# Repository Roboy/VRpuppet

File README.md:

# VRpuppet
An actor struggles to die onstage, but a puppet has to struggle to live

## Installation
Clone the repo into your catkin workspace and build it   

    $ cd path_to_catkin_ws/src
    $ git clone --recurse-submodules https://github.com/Roboy/VRpuppet 
    $ cd ..
    $ catkin_make  
    
Source your workspace  

    $ . devel/setup.bash

## Before you start
Make sure the Host IP as well as the Wifi network and password in VRPuppet/hardware/m3/esp/m3_conrol/src/main.c are set to the correct network (e.g. roboy).   

Then flash VRPuppet/hardware/m3/esp/m3_conrol/src/main.c on to all M3 boards. See M3 Readme.md for how to flash.

## Running the VRCage GUI
In a terminal window start a ROScore  

    $ roscore

In a second terminal window navigate to your catkin workspace, source it as seen above and then start up the VRPuppet Gui by runnung
    
    $ rosrun rqt_gui rqt_gui

and then from the dropdown menu *Plugins->Roboy* choose *vr puppets demo*.  

When operating together with OUI team you might also need to set up a **rosbridge server**, if OUI doesn't have a Linux partition on hand.  

To send commands to the linear actuators  press the GUI's serial node button.  

(**Attention**: the Arduino Mega as well as the motorcontrol shield suffered greatly during the hackathon and should be replaced before resuming operation!)

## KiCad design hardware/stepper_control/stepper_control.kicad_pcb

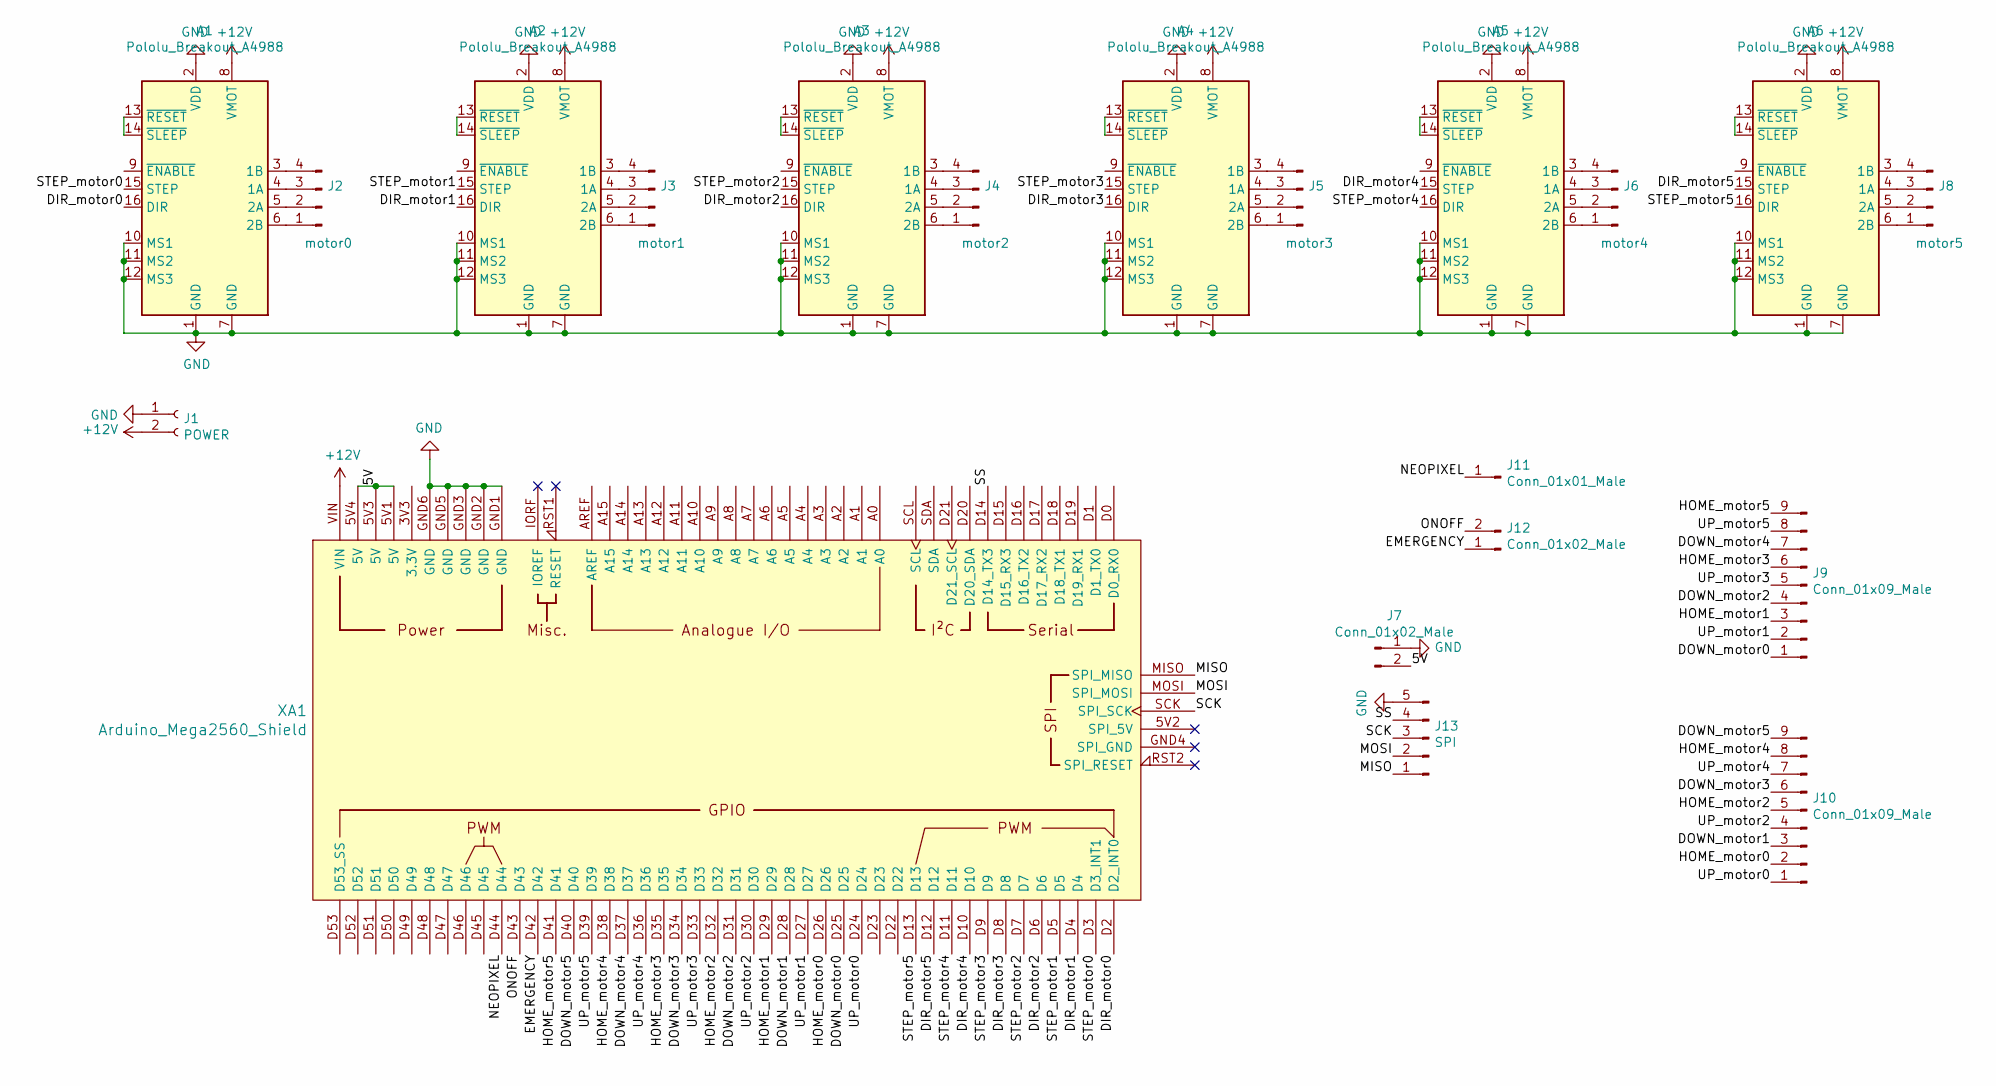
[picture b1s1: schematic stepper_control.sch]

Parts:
A1, A2, A3, A4, A5, A6: Pololu_Breakout_A4988; Pololu_Breakout-16_15.2x20.3mm
J1: POWER; Wago_2060_2_SMD
J2: motor0; PinHeader_1x04_P2.54mm_Vertical
J3: motor1; PinHeader_1x04_P2.54mm_Vertical
J4: motor2; PinHeader_1x04_P2.54mm_Vertical
J5: motor3; PinHeader_1x04_P2.54mm_Vertical
J6: motor4; PinHeader_1x04_P2.54mm_Vertical
J7, J12: Conn_01x02_Male; PinHeader_1x02_P2.54mm_Vertical
J8: motor5; PinHeader_1x04_P2.54mm_Vertical
J9, J10: Conn_01x09_Male; PinHeader_1x09_P2.54mm_Vertical
J11: Conn_01x01_Male; PinHeader_1x01_P2.54mm_Vertical
J13: SPI; PinHeader_1x05_P2.54mm_Vertical
XA1: Arduino_Mega2560_Shield

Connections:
+12V: A1.8 (VMOT), A2.8 (VMOT), A3.8 (VMOT), A4.8 (VMOT), A5.8 (VMOT), A6.8 (VMOT), J1.2, XA1.VIN
/5V: J7.2, XA1.5V1 (5V), XA1.5V3 (5V), XA1.5V4 (5V)
/DIR_motor0: A1.16 (DIR), XA1.D2 (D2_INT0)
/DIR_motor1: A2.16 (DIR), XA1.D4
/DIR_motor2: A3.16 (DIR), XA1.D6
/DIR_motor3: A4.16 (DIR), XA1.D8
/DIR_motor4: A5.15 (STEP), XA1.D10
/DIR_motor5: A6.15 (STEP), XA1.D12
/DOWN_motor0: J9.1, XA1.D25
/DOWN_motor1: J10.3, XA1.D28
/DOWN_motor2: J9.4, XA1.D31
/DOWN_motor3: J10.6, XA1.D34
/DOWN_motor4: J9.7, XA1.D37
/DOWN_motor5: J10.9, XA1.D40
/EMERGENCY: J12.1, XA1.D42
/HOME_motor0: J10.2, XA1.D26
/HOME_motor1: J9.3, XA1.D29
/HOME_motor2: J10.5, XA1.D32
/HOME_motor3: J9.6, XA1.D35
/HOME_motor4: J10.8, XA1.D38
/HOME_motor5: J9.9, XA1.D41
/MISO: J13.1, XA1.MISO (SPI_MISO)
/MOSI: J13.2, XA1.MOSI (SPI_MOSI)
/NEOPIXEL: J11.1, XA1.D44
/ONOFF: J12.2, XA1.D43
/SCK: J13.3, XA1.SCK (SPI_SCK)
/SS: J13.4, XA1.D14 (D14_TX3)
/STEP_motor0: A1.15 (STEP), XA1.D3 (D3_INT1)
/STEP_motor1: A2.15 (STEP), XA1.D5
/STEP_motor2: A3.15 (STEP), XA1.D7
/STEP_motor3: A4.15 (STEP), XA1.D9
/STEP_motor4: A5.16 (DIR), XA1.D11
/STEP_motor5: A6.16 (DIR), XA1.D13
/UP_motor0: J10.1, XA1.D24
/UP_motor1: J9.2, XA1.D27
/UP_motor2: J10.4, XA1.D30
/UP_motor3: J9.5, XA1.D33
/UP_motor4: J10.7, XA1.D36
/UP_motor5: J9.8, XA1.D39
GND: A1.1 (GND), A1.2 (VDD), A1.7 (GND), A1.10 (MS1), A1.11 (MS2), A1.12 (MS3), A2.1 (GND), A2.2 (VDD), A2.7 (GND), A2.10 (MS1), A2.11 (MS2), A2.12 (MS3), A3.1 (GND), A3.2 (VDD), A3.7 (GND), A3.10 (MS1), A3.11 (MS2), A3.12 (MS3), A4.1 (GND), A4.2 (VDD), A4.7 (GND), A4.10 (MS1), A4.11 (MS2), A4.12 (MS3), A5.1 (GND), A5.2 (VDD), A5.7 (GND), A5.10 (MS1), A5.11 (MS2), A5.12 (MS3), A6.1 (GND), A6.2 (VDD), A6.7 (GND), A6.10 (MS1), A6.11 (MS2), A6.12 (MS3), J1.1, J7.1, J13.5, XA1.GND1 (GND), XA1.GND2 (GND), XA1.GND3 (GND), XA1.GND5 (GND), XA1.GND6 (GND)
unnamed: A1.3 (1B), J2.4
unnamed: A1.4 (1A), J2.3
unnamed: A1.5 (2A), J2.2
unnamed: A1.6 (2B), J2.1
unnamed: A1.13 (~RESET), A1.14 (~SLEEP)
unnamed: A2.3 (1B), J3.4
unnamed: A2.4 (1A), J3.3
unnamed: A2.5 (2A), J3.2
unnamed: A2.6 (2B), J3.1
unnamed: A2.13 (~RESET), A2.14 (~SLEEP)
unnamed: A3.3 (1B), J4.4
unnamed: A3.4 (1A), J4.3
unnamed: A3.5 (2A), J4.2
unnamed: A3.6 (2B), J4.1
unnamed: A3.13 (~RESET), A3.14 (~SLEEP)
unnamed: A4.3 (1B), J5.4
unnamed: A4.4 (1A), J5.3
unnamed: A4.5 (2A), J5.2
unnamed: A4.6 (2B), J5.1
unnamed: A4.13 (~RESET), A4.14 (~SLEEP)
unnamed: A5.3 (1B), J6.4
unnamed: A5.4 (1A), J6.3
unnamed: A5.5 (2A), J6.2
unnamed: A5.6 (2B), J6.1
unnamed: A5.13 (~RESET), A5.14 (~SLEEP)
unnamed: A6.3 (1B), J8.4
unnamed: A6.4 (1A), J8.3
unnamed: A6.5 (2A), J8.2
unnamed: A6.6 (2B), J8.1
unnamed: A6.13 (~RESET), A6.14 (~SLEEP)

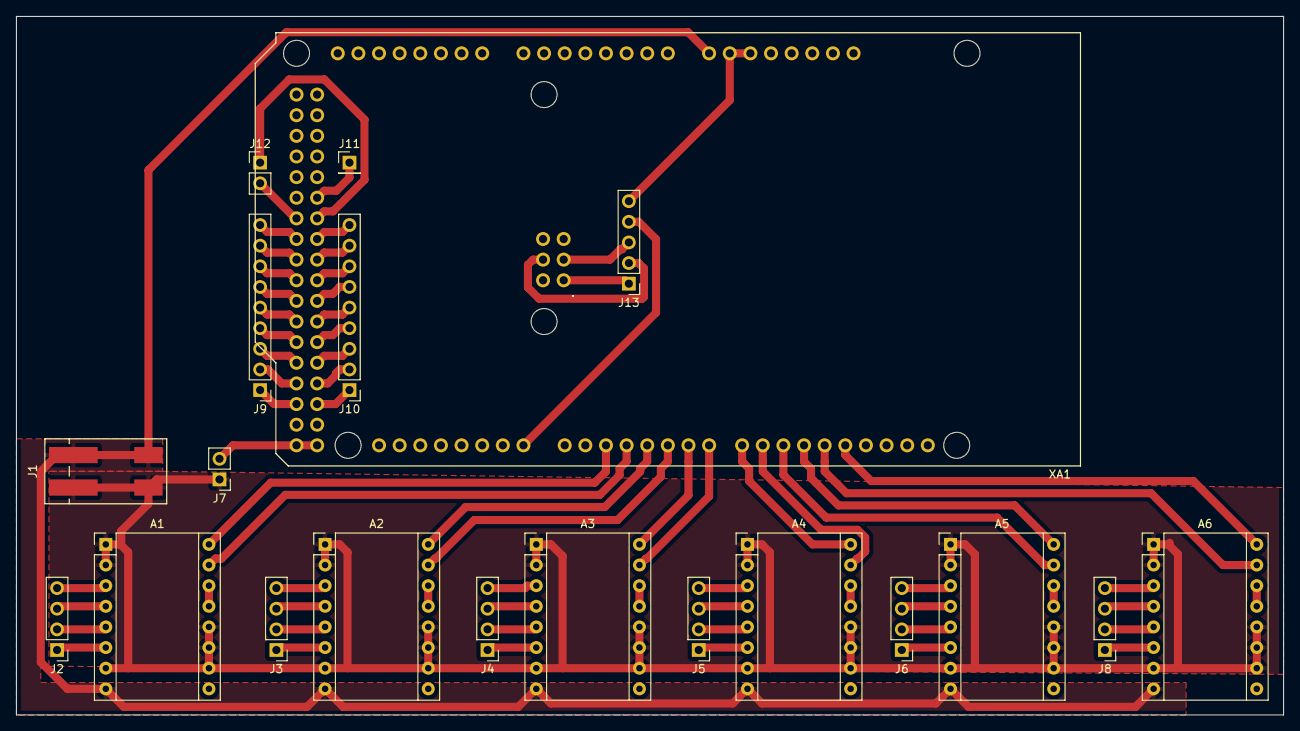
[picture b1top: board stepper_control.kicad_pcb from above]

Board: 2 copper layers, 156.0 x 86.0 mm, 20 parts (0 on the bottom side), 70 nets.

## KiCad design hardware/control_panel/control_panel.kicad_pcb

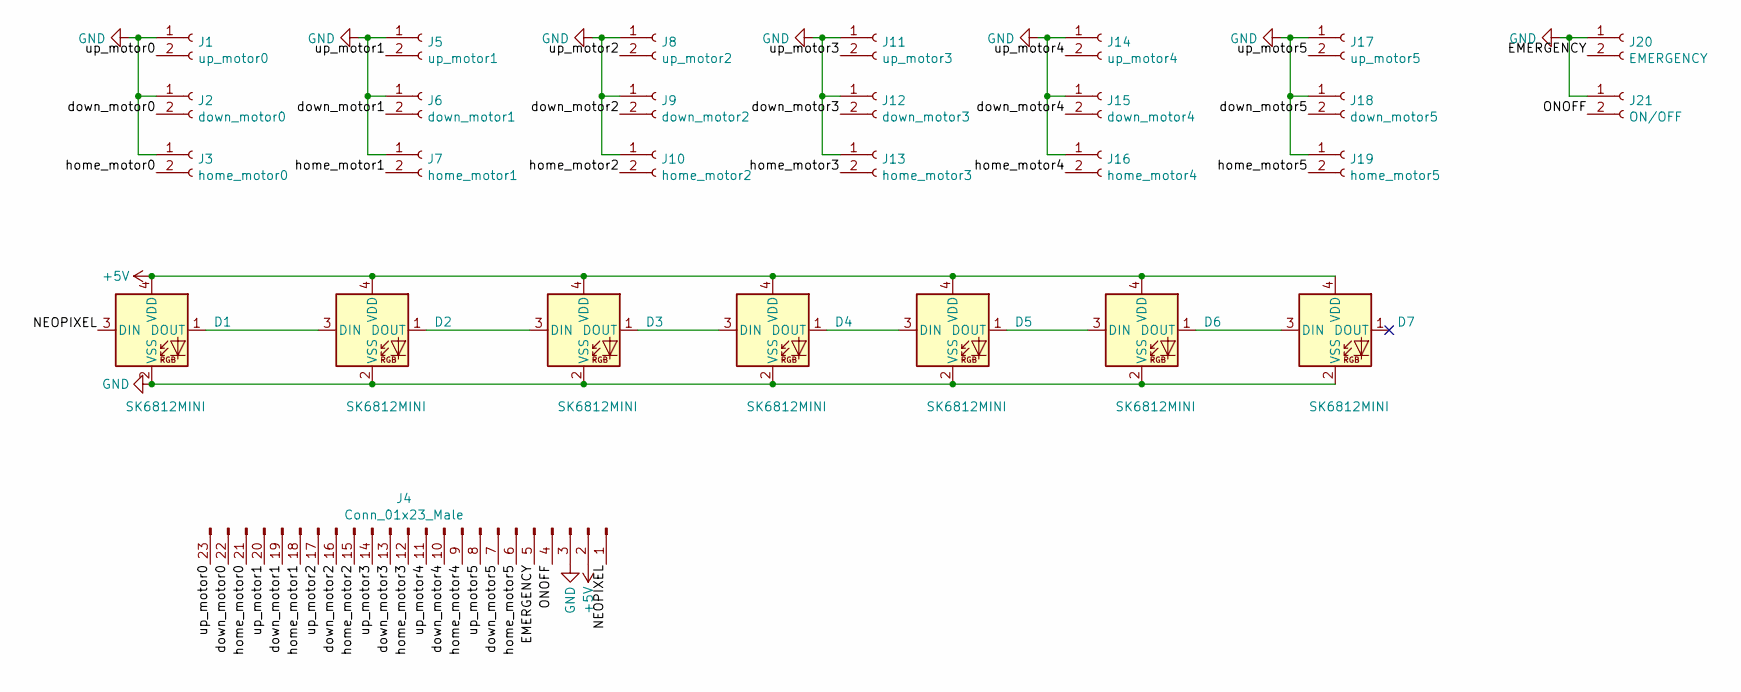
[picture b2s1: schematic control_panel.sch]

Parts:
D1, D2, D3, D4, D5, D6, D7: SK6812MINI; LED_SK6812MINI_PLCC4_3.5x3.5mm_P1.75mm
J1: up_motor0; SW_PUSH_6mm_H7.3mm
J2: down_motor0; SW_PUSH_6mm_H7.3mm
J3: home_motor0; SW_PUSH_6mm_H7.3mm
J4: Conn_01x23_Male; PinHeader_1x23_P2.54mm_Vertical
J5: up_motor1; SW_PUSH_6mm_H7.3mm
J6: down_motor1; SW_PUSH_6mm_H7.3mm
J7: home_motor1; SW_PUSH_6mm_H7.3mm
J8: up_motor2; SW_PUSH_6mm_H7.3mm
J9: down_motor2; SW_PUSH_6mm_H7.3mm
J10: home_motor2; SW_PUSH_6mm_H7.3mm
J11: up_motor3; SW_PUSH_6mm_H7.3mm
J12: down_motor3; SW_PUSH_6mm_H7.3mm
J13: home_motor3; SW_PUSH_6mm_H7.3mm
J14: up_motor4; SW_PUSH_6mm_H7.3mm
J15: down_motor4; SW_PUSH_6mm_H7.3mm
J16: home_motor4; SW_PUSH_6mm_H7.3mm
J17: up_motor5; SW_PUSH_6mm_H7.3mm
J18: down_motor5; SW_PUSH_6mm_H7.3mm
J19: home_motor5; SW_PUSH_6mm_H7.3mm
J20: EMERGENCY; PinHeader_1x02_P2.54mm_Vertical
J21: ON/OFF; PinHeader_1x02_P2.54mm_Vertical

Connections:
+5V: D1.4 (VDD), D2.4 (VDD), D3.4 (VDD), D4.4 (VDD), D5.4 (VDD), D6.4 (VDD), D7.4 (VDD), J4.2
/EMERGENCY: J4.5, J20.2
/NEOPIXEL: D1.3 (DIN), J4.1
/ONOFF: J4.4, J21.2
/down_motor0: J2.2, J4.22
/down_motor1: J4.19, J6.2
/down_motor2: J4.16, J9.2
/down_motor3: J4.13, J12.2
/down_motor4: J4.10, J15.2
/down_motor5: J4.7, J18.2
/home_motor0: J3.2, J4.21
/home_motor1: J4.18, J7.2
/home_motor2: J4.15, J10.2
/home_motor3: J4.12, J13.2
/home_motor4: J4.9, J16.2
/home_motor5: J4.6, J19.2
/up_motor0: J1.2, J4.23
/up_motor1: J4.20, J5.2
/up_motor2: J4.17, J8.2
/up_motor3: J4.14, J11.2
/up_motor4: J4.11, J14.2
/up_motor5: J4.8, J17.2
GND: D1.2 (VSS), D2.2 (VSS), D3.2 (VSS), D4.2 (VSS), D5.2 (VSS), D6.2 (VSS), D7.2 (VSS), J1.1, J2.1, J3.1, J4.3, J5.1, J6.1, J7.1, J8.1, J9.1, J10.1, J11.1, J12.1, J13.1, J14.1, J15.1, J16.1, J17.1, J18.1, J19.1, J20.1, J21.1
unnamed: D1.1 (DOUT), D2.3 (DIN)
unnamed: D2.1 (DOUT), D3.3 (DIN)
unnamed: D3.1 (DOUT), D4.3 (DIN)
unnamed: D4.1 (DOUT), D5.3 (DIN)
unnamed: D5.1 (DOUT), D6.3 (DIN)
unnamed: D6.1 (DOUT), D7.3 (DIN)

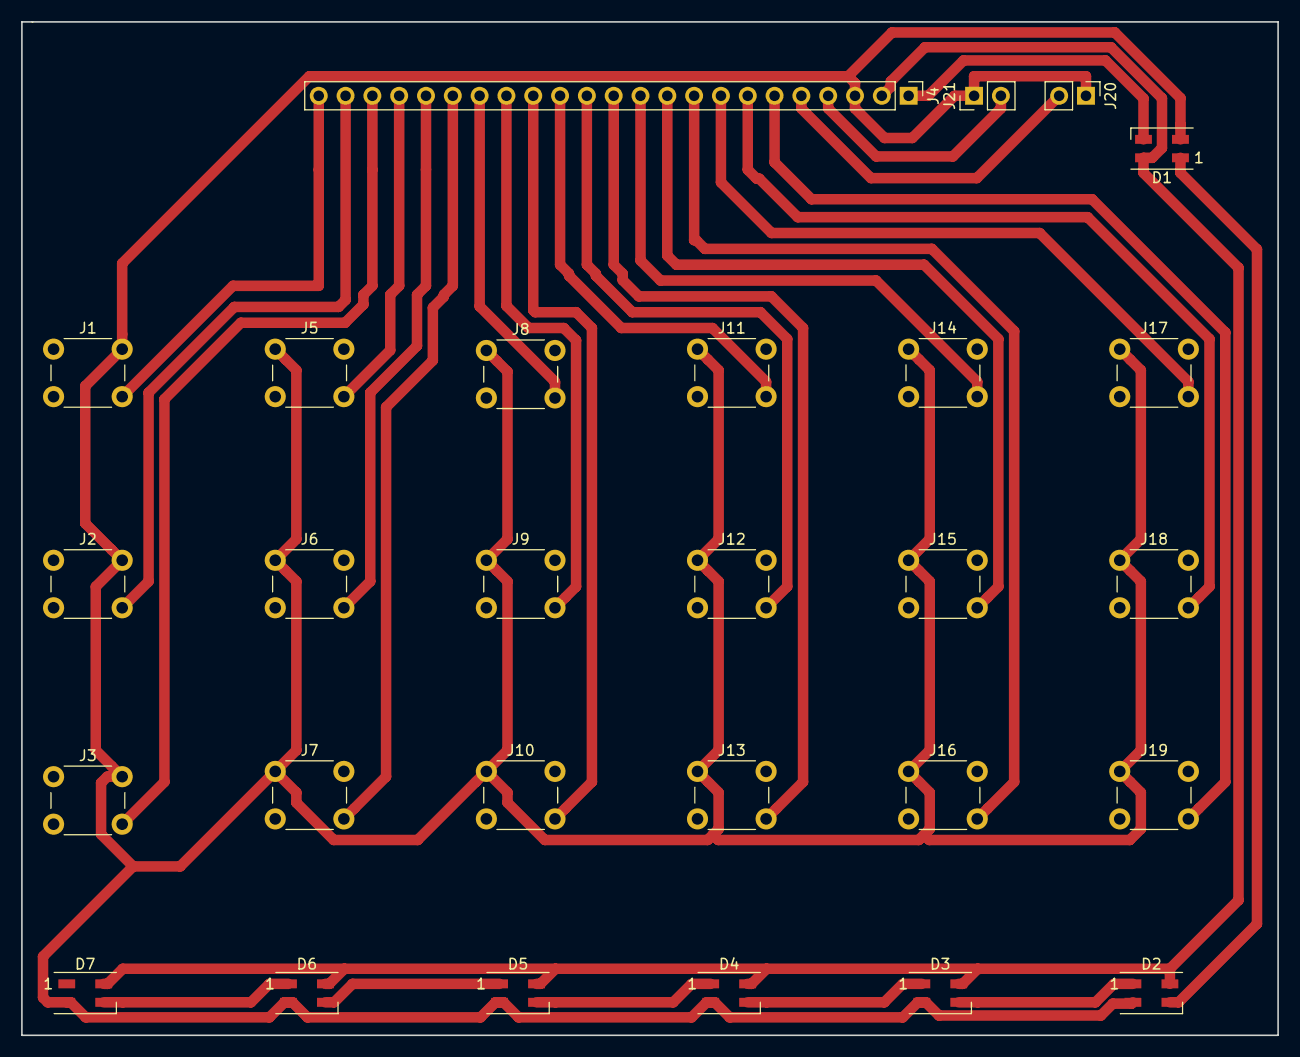
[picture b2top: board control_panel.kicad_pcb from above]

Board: 2 copper layers, 119.0 x 96.0 mm, 28 parts (0 on the bottom side), 29 nets.

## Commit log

2019-05-27 initial
2019-06-20 directly applying q_targets
2019-06-21 with rqt
2019-06-21 draft
2019-06-23 hehehe
2019-06-26 simons mama
2019-06-27 works for the arms
2019-06-27 works
2019-06-29 with new cage
2019-07-02 with control panel
2019-07-03 with stepper control pcb
2019-07-03 with spi
2019-07-03 with slave select
2019-07-08 with rosserial control for linear actuators
2019-07-10 works with real cage
2019-07-11 with pull releas and neopixel pins
2019-07-16 with init
2019-07-16 with more stuff
2019-07-17 added e-stop client
2019-07-17 e_stop
2019-07-17 e_stop done
2019-07-17 works with cage
2019-08-22 changed IP and started bugfixes
2019-08-22 added submodule m3
2019-08-22 added submodule m3 & changed IP
2019-08-22 added m3 submodule
2019-08-23 fixed submodule dep.
2019-08-23 preparing ff pull
2019-08-27 started working on demo code + gui
2019-08-29 motors ALL STOPPING at the same time, not all moving on continue
2019-08-29 ALL motors stopping and continuing on button pushed
2019-08-29 VRPuppets_demo: added single_motor_setpoint boxes etc.
2019-08-29 displaying init setpoint in gui
2019-08-30 DEMO: cleaned up, added/improved comments, started on transition servicecallbackCC
2019-08-30 state transmission service in work
2019-08-30 setalltopositionmode added, keeping motors in init pos
2019-09-01 added obstacle reached CB, fixed alltodisplacement issues, reading out current pos status on setpositionmodeforall
2019-09-01 demo ready to rumble! - all demostuff working.
2019-09-07 added doxyfile, started docu, added OUI msgs
2019-09-25 changed vr_puppets_demo to vr_puppets, fixed conflicts
2019-09-25 added documentation
2019-09-29 changed m3 readme
2019-09-29 added gui img
